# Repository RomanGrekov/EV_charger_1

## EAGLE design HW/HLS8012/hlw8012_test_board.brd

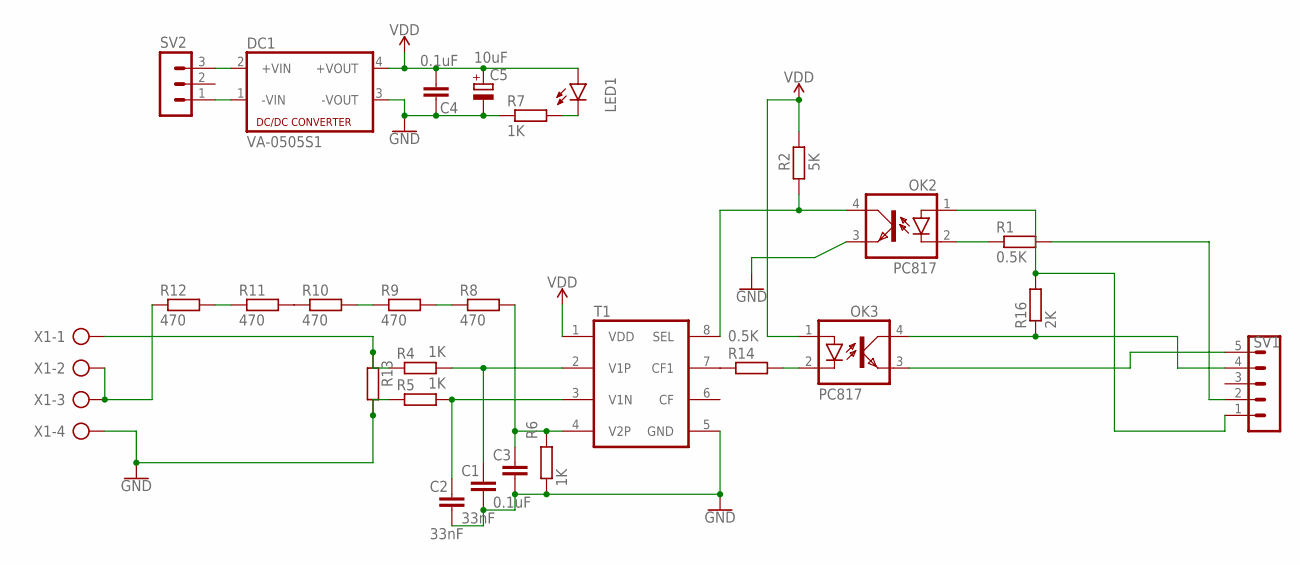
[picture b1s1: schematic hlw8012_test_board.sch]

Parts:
C1, C2: 33nF; C0805
C3, C4: 0.1uF; C0805
C5: 10uF; 153CLV-0405
DC1: VA-0505S1; 4SIL
LED1: LED3MM
OK2, OK3: PC817; DIL04
R1, R14: 0.5K; M0805
R2: 5K; M0805
R4, R5, R6, R7: 1K; M0805
R8, R9, R10, R11, R12: 470; M0805
R13: PMD
R16: 2K; M0805
SV1: MA05-1
SV2: MA03-1
T1: HLW8012; SO8
X1: AK300/4

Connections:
GND: C1.2, C2.2, C3.2, C4.1, C5.-, DC1.3 (-VOUT), OK2.3 (EMIT), R5.1, R6.1, R7.1, R13.1, T1.5 (GND), X1.4
unnamed: OK2.1 (A), R16.2, SV1.1
unnamed: OK2.2 (C), R1.1
unnamed: R1.2, SV1.2
unnamed: OK2.4 (COL), R2.1, T1.8 (SEL)
unnamed: R14.1, T1.7 (CF1)
unnamed: OK3.4 (COL), R16.1, SV1.4
unnamed: OK3.2 (C), R14.2
unnamed: DC1.1 (-VIN), SV2.1
unnamed: DC1.2 (+VIN), SV2.3
unnamed: OK3.3 (EMIT), SV1.5
unnamed: R4.1, R13.2, X1.1
unnamed: LED1.K (C), R7.2
unnamed: C1.1, R4.2, T1.2 (V1P)
unnamed: C2.1, R5.2, T1.3 (V1N)
unnamed: C3.1, R6.2, R8.2, T1.4 (V2P)
unnamed: R8.1, R9.2
unnamed: R9.1, R10.2
unnamed: R10.1, R11.2
unnamed: R11.1, R12.2
unnamed: R12.1, X1.2, X1.3
VDD: C4.2, C5.+, DC1.4 (+VOUT), LED1.A, OK3.1 (A), R2.2, T1.1 (VDD)

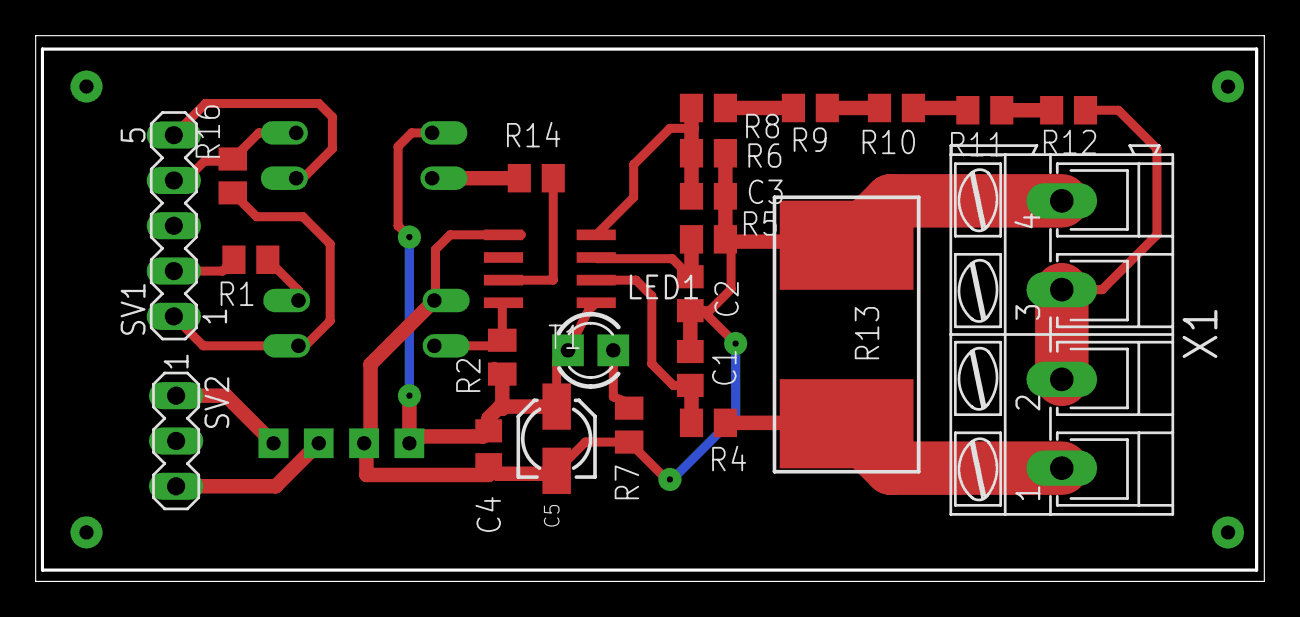
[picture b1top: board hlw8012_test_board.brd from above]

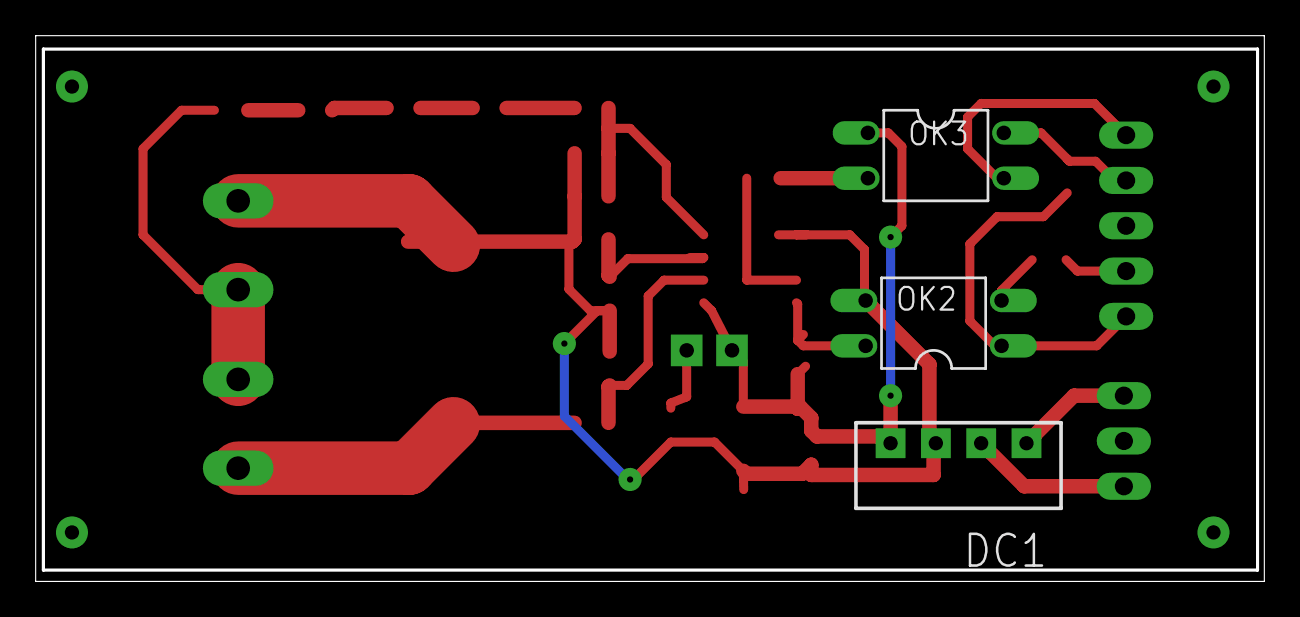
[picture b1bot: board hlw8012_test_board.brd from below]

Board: 2 copper layers, 68.9 x 30.6 mm, 27 parts (3 on the bottom side), 22 nets.

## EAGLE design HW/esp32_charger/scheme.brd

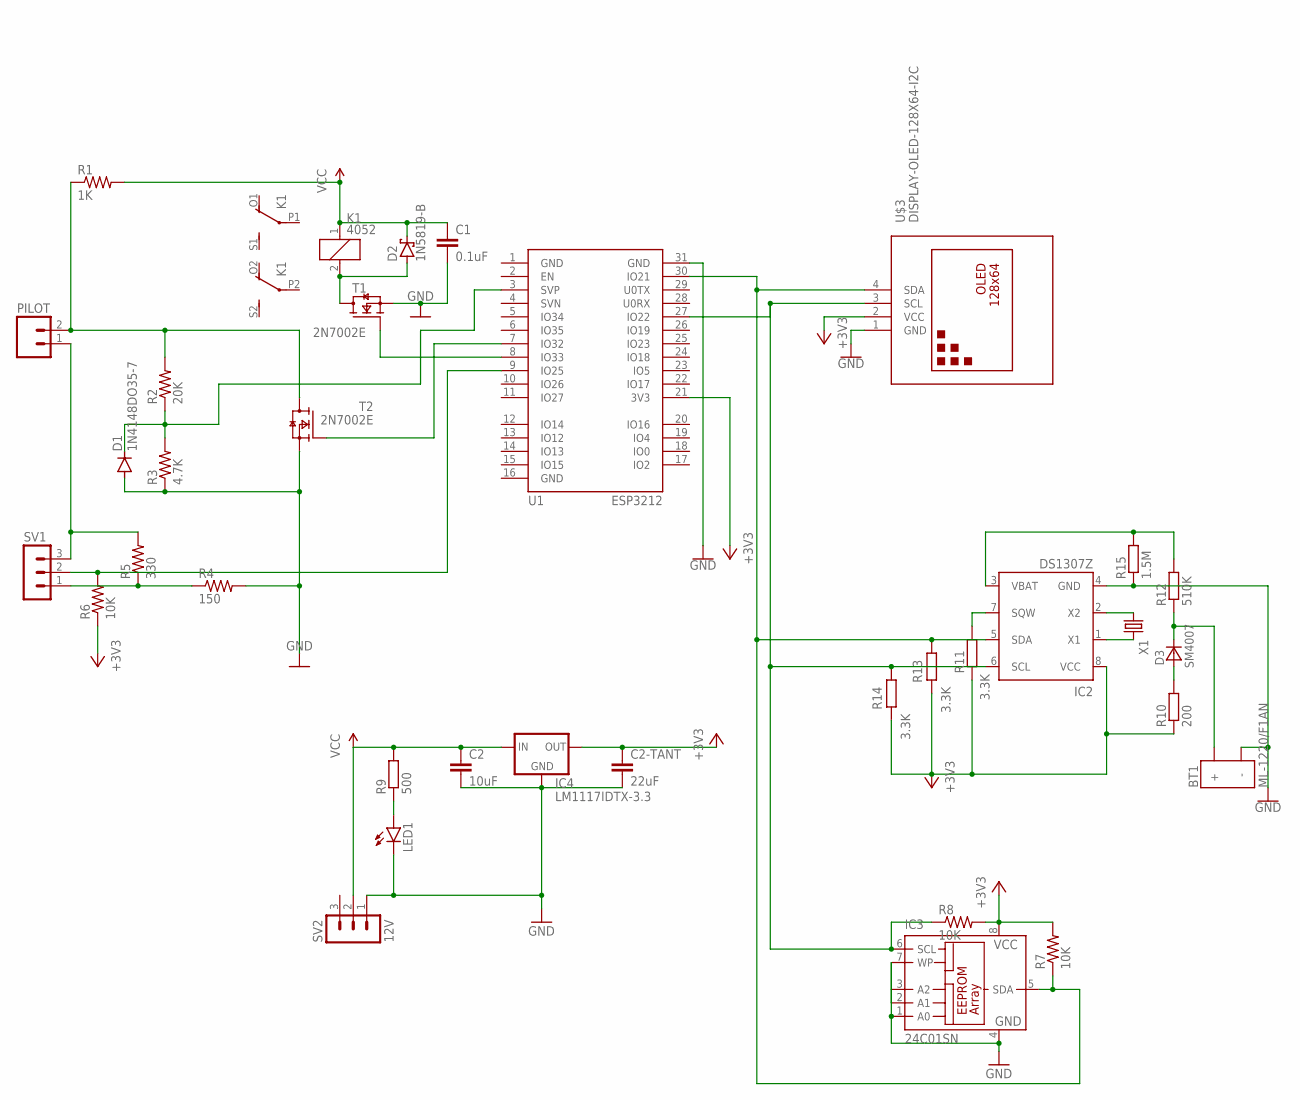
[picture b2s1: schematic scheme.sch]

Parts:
BT1: ML-1220/F1AN; ML-1220/F1BN
C1: 0.1uF; CAP-PTH-SMALL-KIT
C2: 10uF; C0805
C2-TANT: 22uF; C3216
D1: 1N4148DO35-7; DO35-7
D2: 1N5819-B; DO41-7.6
D3: SM4007; MELF-MLL41
IC2: DS1307Z; SOIC8
IC3: 24C01SN; SO-08
IC4: LM1117IDTX-3.3; TO252
K1: 4052; F4052
LED1: LEDCHIP-LED0805; CHIP-LED0805
PILOT: SPARKFUN_M02POLAR_LOCK; SPARKFUN_MOLEX-1X2_LOCK
R1: 1K; SPARKFUN_AXIAL-0.5
R2: 20K; SPARKFUN_AXIAL-0.5
R3: 4.7K; SPARKFUN_AXIAL-0.5
R4: 150; SPARKFUN_AXIAL-0.5
R5: 330; SPARKFUN_AXIAL-0.5
R6, R7, R8: 10K; SPARKFUN_AXIAL-0.5
R9: 500; R0805
R10: 200; R0805
R11, R13, R14: 3.3K; R0805
R12: 510K; R0805
R15: 1.5M; R0805
SV1: MA03-1
SV2: 12V; MA03-1
T1, T2: 2N7002E; SOT23
U1: ESP3212
U$3: DISPLAY-OLED-128X64-I2C
X1: CRYSTALS-NOGND-WATCH-3X8; WATCH-3X8

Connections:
+3V3: C2-TANT.1, IC2.8 (VCC), IC3.8 (VCC), IC4.TAB (OUT), R6.P$1 (1), R7.P$2 (2), R8.P$2 (2), R10.1, R11.1, R13.2, R14.2, U1.21 (3V3), U$3.2 (VCC)
GND: BT1.NEG (-), C1.2, C2.2, C2-TANT.2, D1.A, IC2.4 (GND), IC3.1 (A0), IC3.2 (A1), IC3.3 (A2), IC3.4 (GND), IC3.7 (WP), IC4.1 (GND), LED1.C, R3.P$1 (1), R4.P$2 (2), R15.1, SV2.1, T1.2 (S), T2.2 (S), U1.1 (GND), U1.16 (GND), U1.31 (GND), U$3.1 (GND)
unnamed: LED1.A, R9.1
unnamed: IC2.1 (X1), X1.2
unnamed: T1.1 (G), U1.8 (IO33)
unnamed: D2.A, K1.2, T1.3 (D)
unnamed: T2.1 (G), U1.7 (IO32)
unnamed: PILOT.2, R1.P$1 (1), R2.P$2 (2), T2.3 (D)
unnamed: D1.C, R2.P$1 (1), R3.P$2 (2), U1.3 (SVP)
unnamed: R4.P$1 (1), R5.P$1 (1), SV1.1
unnamed: PILOT.1, R5.P$2 (2), SV1.3
unnamed: R6.P$2 (2), SV1.2, U1.9 (IO25)
unnamed: IC2.7 (SQW), R11.2
unnamed: IC2.2 (X2), X1.1
unnamed: IC2.6 (SCL), IC3.6 (SCL), R8.P$1 (1), R14.1, U1.27 (IO22), U$3.3 (SCL)
unnamed: IC2.5 (SDA), IC3.5 (SDA), R7.P$1 (1), R13.1, U1.30 (IO21), U$3.4 (SDA)
unnamed: IC2.3 (VBAT), R12.2, R15.2
unnamed: BT1.POS (+), D3.C, R12.1
unnamed: D3.A, R10.2
VCC: C1.1, C2.1, D2.C, IC4.2 (IN), K1.1, R1.P$2 (2), R9.2, SV2.2

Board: 2 copper layers, 35 parts (0 on the bottom side), 20 nets, no tracks yet.

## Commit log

2019-05-06 Added scheme. Added eeprom
2019-08-04 Updated project and gitignore
2019-08-04 gitignore reinit
2019-08-04 Added bare esp32 and ds1307
2019-08-24 Added lib
2019-08-24 Added hlw8012 dirst revision board
2019-08-26 Refactored hlw board
2019-10-31 Updated hlw board. Added libs
2019-10-31 Added initial pilot scheme

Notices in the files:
parts and their libraries:
SparkFun-PowerSymbols: Licensing: Creative Commons ShareAlike 4.0 International - https://creativecommons.org/licenses/by-sa/4.0
diy-modules: Released under the Creative Commons Attribution 4.0 International License: http://creativecommons.org/licenses/by/4.0
